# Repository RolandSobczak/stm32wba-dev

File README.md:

# wb55-dev

Dev board na **STM32WB55CGU6** (Bluetooth 5.x + 802.15.4) z pełnym torem
zasilania przeniesionym z `gps_tracker-6l`, pamięcią masową na płytce, anteną
w laminacie i wszystkimi wolnymi nóżkami na goldpinach 2,54 mm.

```
USB-C ──▶ BQ25896 ──┬──▶ SYS ──▶ TPS63020 ──▶ 3V3 ──┬──▶ STM32WB55CGU6 ──▶ MLPF ──▶ antena PCB
  │  (Rd 5.1k + ADC) │                              │        │
  └── D+/D- ─────────│──────────────────────────────│────────┘
                     └──▶ Li-Po 1S                  ├──▶ SD NAND 2 Gbit (SPI1)
                          │                         │
                          └──▶ BQ27441 (gauge)      └──▶ dwie listwy 1×12 (2,54 mm)
                                  │
                                  └── I2C1 ─────────────────┘
```

Obrys 32,5 × 59,6 mm, sześć warstw, narożniki R2,0, **dwa zestawy otworów**:
cztery M3 (⌀3,2) odsunięte 3,5 mm od krawędzi
po obrysie 25,8 × 42,2.

## Co jest wzięte z `gps_tracker-6l`

Tor zasilania w całości, razem z komentarzami uzasadniającymi — one są
w tych plikach wartością, a nie dekoracją:

| blok | część | skąd |
|---|---|---|
| gniazdo USB-C + ESD | GCT USB4085-GF-A, USBLC6-2SC6 | `power.ato` |
| ładowarka NVDC | TI BQ25896 (I2C 0x6B) | `power.ato` |
| gauge | TI BQ27441-G1A (I2C 0x55), bocznik 10 mΩ po stronie dodatniej | `power.ato` |
| 3V3 | TI TPS63020, buck-boost | `power.ato` |
| gniazdo ogniwa | Molex PicoBlade 53261-0371 — **ten sam pakiet wchodzi w obie płytki** | `power.ato` |
| stos | JLC06161H-7628, prepreg 0,2104 mm pod F.Cu | `tools/board_setup.py` |
| obrys, otwory, wylewki, klasy sieci | — | `tools/board_setup.py` |

Zmieniły się trzy rzeczy i każda ma powód w pliku:

1. **CC bez PD.** STM32WB55 nie ma UCPD (potwierdzone listą peryferiów
   w `STM32WB55CGUx.xml`). Zamiast negocjacji PD: dwa Rd 5,1 kΩ i pomiar
   napięcia na obu CC przetwornikiem — źródło USB-C ogłasza swój prąd prądem
   Rp niezależnie od PD. Szczegóły, progi i sekwencja dla firmware'u:
   [Zasilanie z USB](#zasilanie-z-usb--co-ustala-prąd-wejściowy).
   Efekt uboczny jest korzystny: Rd działa też przy martwym procesorze,
   więc płytka prosto z montażu dostaje VBUS.
2. **Dzielnik VBUS_SENSE wypadł** — bez maszyny stanów PD nie ma czego nim
   mierzyć w milisekundach, a napięcie VBUS czyta ADC ładowarki po I2C.
3. **Gauge `DRZR` → `DRZT`** — ten sam układ, inna nawijka. `DRZR` ma na LCSC
   stan 0.

## BOM

34 pozycje, wszystkie na stanie LCSC (sprawdzone 2 października 2026),
około **$30,50** za komplet części na jedną sztukę w cenach detalicznych.
Najdroższe: STM32WB55CGU6 $9,04 · SD NAND $8,66 · BQ25896 $3,52 ·
BQ27441 $2,52 · USB-C $1,41.

Pełna lista: `build/builds/dev/dev.bom.csv` (powstaje przy `ato build`).

Trzy pozycje odziedziczone z trackera miały na LCSC stan zero i zostały
podmienione — w komentarzach przy nich stoją nowe numery:

| było | jest | dlaczego |
|---|---|---|
| C25804 10 kΩ | **C98220** YAGEO RC0603FR-0710KL | stan 0 |
| C96446 10 µF 25 V | **C479655** 0603X106M250NT | stan 0 |
| C346479 bocznik 10 mΩ | **C105362** FMF06FTHR010-LH | stan 0; nowy ma ±1 %, 1 W i TCR ±70 ppm/°C, czyli lepiej niż poprzednik |

Poza BOM-em (kupowane osobno albo niekupowane wcale): dwie listwy goldpinów
1×12 2,54 mm, złącze SWD Samtec SHF-105-01-L-D-RA, cztery pady pomiarowe
i antena — ta ostatnia jest kształtem miedzi, nie elementem.

## Mapa wyprowadzeń

Układ ma **30 nóżek I/O i wszystkie są rozdane.** Siedem wolnych wychodzi
na prawą listwę, PA15 na lewą jako CS, PB5 na diodę.

```
 1 VBAT   +3V3           17 PA8   USART1_CK      33 VLXSMPS SMPS
 2 PC14   LSE_IN         18 PA9   USART1_TX      34 VDDSMPS +3V3
 3 PC15   LSE_OUT (0R)   19 PB2   CHG_STAT       35 VDD     +3V3
 4 PH3    BOOT0          20 VDD   +3V3           36 PA10    USART1_RX
 5 PB8    PMIC_SCL       21 RF1   -> MLPF        37 PA11    USB_D_N
 6 PB9    PMIC_SDA       22 VSSRF GND            38 PA12    USB_D_P
 7 NRST   reset          23 VDDRF +3V3           39 PA13    SWDIO
 8 VDDA   +3V3           24 OSC_OUT 32 MHz       40 VDDUSB  +3V3
 9 PA0    CC1 (ADC_IN5)  25 OSC_IN  32 MHz       41 PA14    SWCLK
10 PA1    CC2 (ADC_IN6)  26 AT0   bez sieci      42 PA15    EXT_CS
11 PA2    LPUART1_TX     27 AT1   bez sieci      43 PB3     SWO
12 PA3    LPUART1_RX     28 PB0   CHG_INT        44 PB4     GAUGE_INT
13 PA4    SD_CS          29 PB1   CHG_CE         45 PB5     LED
14 PA5    SD_CLK         30 PE4   CHG_PG         46 PB6     USART1 alt
15 PA6    SD_MISO        31 VFBSMPS SMPS         47 PB7     USART1 alt
16 PA7    SD_MOSI        32 VSSSMPS GND          48 VDD     +3V3
                                                 49 EP      GND  (jedyna masa!)
```

**Szycie liczy się z kształtem padu, nie z jego obrysem.** Pady termiczne
z EasyEDA to wielokąty: TPS63020 ma grzebień wycięć na nóżki, a BQ27441
kształt teowy ze środkową belką 2,0 × 1,95 mm i dwoma pionowymi pasami
szerokimi na 0,22 mm. Siatka rozłożona na prostokącie obrysu stawiałaby
przelotki w wycięciach — na gołym laminacie między nóżkami. Dlatego każda
pozycja jest sprawdzana dwa razy: czy **cała** przelotka mieści się
w miedzi padu (środek plus cztery punkty na obwodzie) i czy nie wchodzi
w cudzą miedź na którejkolwiek warstwie — przelotka jest przelotowa, więc
przebija też In2, In3 i B.Cu, gdzie leżą sygnały.

**Masa układu jest wyłącznie na padzie pod obudową** — UFQFPN-48 nie ma ani
jednej nóżki VSS. Pad dostaje **siatkę 5×5 = 25 przelotek** 0,50/0,30 mm
w rastrze 1,12 mm, stawianą przez `tools/board_setup.py`. Bez niej masa
procesora wisiałaby na wylewce F.Cu, a płaszczyzna In1 leży 0,2104 mm niżej.

**Przelotki leżą w padzie, więc muszą być zalane — i to przesądziło o liczbie
warstw.** Kanał przelotki ⌀0,3 przez laminat 1,6 mm ma 0,113 mm³; na padzie
5,5 × 5,5 mm leży przy szablonie 0,12 mm i pokryciu 60 % około 1,09 mm³
solderu. Czyli **już dziewięć otwartych przelotek ma pojemność porównywalną
z całym solderem**, a dwadzieścia pięć — dwa i pół raza większą. Niezalana
siatka oznacza zagłodzoną spoinę, a tu jest to jedyna masa układu.

Wycena JLCPCB (100 × 100 mm, 5 szt., FR-4 1,6 mm):

| konfiguracja | Via Covering | Via Plating | razem |
|---|---|---|---|
| 4 warstwy, Plugged albo Untented | €0,00 | — | **€7,13** |
| 4 warstwy, **Epoxy Filled & Capped** | €15,85 | €3,06 | **€26,03** |
| 6 warstw, Epoxy Filled & Capped (domyślne) | €0,00 | €0,00 | **€28,52** |

Dopłata na czterech warstwach to **€18,91**; „Horizontal Electroless Copper
Plating" (€3,06) jest przy zalewaniu wymuszone. **Stąd sześć warstw**: za
€2,49 różnicy zalewanie wchodzi w cenę, a przy okazji dochodzą dwie warstwy
sygnałowe (In2, In3).

Dwa haczyki, oba przy zamawianiu, nie w pliku płytki: produkcja trwa **8–9
dni** zamiast 3–4 (skrócenie do 3–4 kosztuje €118,01), a sześć warstw **nie
obsługuje HASL** — zostaje OSP albo ENIG. Przy rastrze 0,5 mm i padzie
termicznym ENIG i tak jest sensowniejszy, bo daje płaskie pady.

**Wszystkie wiertła mają 0,3 mm i ani dziesiątej mniej.** W formularzu
JLCPCB „Min via hole size/diameter" tylko pierwszy próg — `0.3mm/(0.4/0.45mm)`
— jest bezpłatny; każdy niższy podnosi cenę całego zamówienia. Dlatego
przelotka sygnałowa to **0,5/0,3** (a nie 0,6/0,3 jak wcześniej — próg
dopuszcza średnice od 0,4 mm, więc 0,1 mm wraca na trasowanie), a ta w padzie
**0,5/0,3** z sufitem narzuconym przez samo JLCPCB: *„Vias should be at most
0.5 mm in diameter to avoid incomplete filling. Vias violating this size will
be left unfilled."*

`board_setup.py` sprawdza to przy każdym uruchomieniu i wypisuje każdą
przelotkę z wiertłem poniżej progu — razem z pozycją i siecią.

Listwy (opis i uzasadnienie kolejności w `headers.ato`):

```
LEWA / J2 (SPI1 + rozszerzenia)     PRAWA / J1 (zasilanie, I2C, GPIO)
 1 SD_CLK    7 GND                   1 +3V3       7 PB6
 2 PA9       8 SD_MOSI               2 PA3        8 PB7
 3 PA10      9 GND                   3 PA8        9 PA2
 4 GND      10 EXP_P4                4 PMIC_SCL  10 +3V3
 5 EXT_CS   11 EXP_P5                5 GND       11 GND
 6 SD_MISO  12 EXP_P6                6 PMIC_SDA  12 BOOT0
```

Układ pozycji powstał przy trasowaniu, nie przy planowaniu — kolejność
widać dopiero wtedy, gdy linie zaczynają się krzyżować. Przeniesieniem
tego z płytki z powrotem do `.ato` zajmuje się `tools/sync_headers.py`.

**Na lewej listwie nie ma zasilania, tylko masa** (pozycje 4, 7, 9).
+3V3 przeniosło się w całości na prawą, gdzie stoi na dwóch pozycjach
(1 i 10) razem z dwiema masami (5 i 11) — przy listwie, z której coś się
zasila, jedna para na dwanaście pozycji oznacza długą drogę powrotną.
`VBUS` i `SYS` zniknęły z listew; obie sieci nadal są na płytce, tylko
nie wychodzą na goldpiny.

**Trzy zapasowe wyprowadzenia ekspandera (P4, P5, P6) wyszły na J2.**
P3 i P7 zostają na płytce. Osiem wyprowadzeń po drugiej stronie I2C jest
więcej warte na listwie niż w powietrzu.

### Jakie magistrale z tego wychodzą

Lista peryferiów w `STM32WB55CGUx.xml` kończy się na **I2C1, I2C3, USART1,
LPUART1, SPI1, QUADSPI**. Nie ma SPI2, nie ma I2C2, nie ma USART2 — na
większej obudowie STM32WB55 ma SPI2, ale jego nóżki (PB12–PB15, PC2/PC3,
PD0–PD4) nie wychodzą poza kostkę w UFQFPN-48.

| magistrala | nóżki | gdzie |
|---|---|---|
| **LPUART1** | PA2 / PA3 | J1-2, J1-3 |
| **USART1** | PA9 / PA10, albo PB6 / PB7 | J1-5/6 albo J1-9/10 |
| **I2C1** | PB8 / PB9 | J1-7, J1-8 |
| **SPI1** | PA5 / PA6 / PA7 + CS PA15 | J2-5/6/8 + J2-9 |

**QUADSPI jest tu martwy.** `QUADSPI_CLK` istnieje wyłącznie na PA3, a PA3 to
jedyny możliwy `LPUART1_RX` (drugi, PA12, to USB D+). `BK1_IO0` tylko na PB9,
`BK1_IO1` tylko na PB8 — czyli na magistrali PMIC-a. Włączenie QSPI
kosztowałoby drugi UART i sterowanie ładowarką naraz.

**Drugie SPI, gdyby było potrzebne**, ma dwie drogi i wykluczają się: dwa
układy na jednej magistrali SPI1 (SD NAND na PA4, zewnętrzny na PA15 — i to
przewiduje ta płytka), albo **USART1 w trybie synchronicznym** — `USART1_CK`
na PA8 robi z niego mastera SPI (PA8 jako SCK, PA9 jako MOSI, PA10 jako
MISO), kosztem drugiego UART-u i przy ~8 Mbit/s zamiast 32. Obie
konfiguracje chodzą na tych samych pozycjach listwy, więc przejście między
nimi to zmiana w firmware, nie przelutowanie.

**I2C na listwie TO JEST magistrala zasilania.** J1-7 i J1-8 to ta sama para,
na której wiszą BQ25896 (0x6B) i BQ27441 (0x55). Drugiej nie ma: I2C3 ma na
tym pakiecie po jednej nóżce na sygnał (`SCL` tylko PA7, `SDA` tylko PB4)
i obie są zajęte. Trzy konsekwencje opisane w nagłówku `headers.ato`: adresy
`0x6B` (kolizja z IMU ST) i `0x55` są zajęte, zwarcie na przewodzie zabiera
sterowanie ładowarką (watchdog I2C 40 s cofa ją do 500 mA), a pull-upy 4,7 kΩ
są dobrane pod płytkę — 20 cm przewodu spycha magistralę ze 400 na 100 kHz.

**Magistrala SPI1 na lewej listwie to ta sama, na której siedzi SD NAND**,
i inaczej się nie da: `SPI1_SCK` istnieje tylko na PA1 (CC2), PA5 (SD_CLK)
i PB3 (SWO), a `SPI1_MISO` tylko na PA6 (SD_MISO), PA11 (USB) i PB4
(GAUGE_INT) — ani jednej wolnej nóżki.

Pozycje 5–9 lewej listwy były puste — niosły SWD, zanim na płytkę weszło
osobne złącze ARM Cortex Debug 2×5. Wcześniejsza wersja tego opisu zakazywała
ich ponownego użycia; **ten argument wiąże dopiero od pierwszej
wyprodukowanej sztuki**, a takiej nie ma.

Wejście w DFU: zworka z pinu 11 (BOOT0) na pin 3 (+3V3) lewej listwy i reset.

## Przyciski i diody

Opis i uzasadnienia w `ui.ato`. Dwie warstwy, bo dwie klasy problemów.

### Przyciski systemowe — zero nóżek procesora

| przycisk | podłączenie | co już było na płytce |
|---|---|---|
| **RESET** (`SW1`) | NRST → masa | 100 nF + 100 k podciągnięcie z `mcu.ato` |
| **BOOT0** (`SW2`) | BOOT0 → +3V3 | 10 k ściągnięcie z `mcu.ato` |

NRST i BOOT0 to nie GPIO, więc te przyciski nie kosztują ani jednego
wyprowadzenia. Nie wprowadzają też **ani jednej nowej sieci** — obie
końcówki wiszą na `NRST`, `BOOT0`, `GND` i `+3V3`. Gest jest standardowy:
trzymasz BOOT0, stukasz RESET, jesteś w bootloaderze. Wcześniej reset
wymagał zwarcia pinów listwy albo odcięcia zasilania, a DFU — drutu z J2-11
na J2-3.

Przycisk: **C&K KMR221GLFS** (C72443), gull-wing, 4,6 × 2,8 × 1,9 mm,
50 mA / 100 000 cykli. Ekran (nóżka 5) idzie na masę — nielutowany zbiera
ładunek z palca i oddaje go w sygnał, co przy RESET oznacza płytkę
resetującą się od dotknięcia obok.

Rezystora 100 Ω szeregowo przy RESET **nie ma świadomie**: przycisk zwiera
naładowane 100 nF przez styki, co je powoli eroduje, ale AN2586 i wszystkie
płytki Nucleo oraz Discovery łączą go wprost.

### Ekspander I/O — TCA6408A

VQFN-16 **3,0 × 3,0 mm** (LCSC C181499), na magistrali zasilania pod
**adresem 0x20** (ADDR na masie), czyli daleko od ładowarki `0x6B`
i gauge'a `0x55`.

```
P0  dioda czerwona      P4  wolne
P1  dioda zielona       P5  wolne
P2  przycisk użytk.     P6  wolne
P3  wolne               P7  wolne
```

Dwie diody i jeden przycisk, nie trzy i dwa — wersja z trzema diodami
i dwoma przyciskami zajmowała 166,5 mm² i nie mieściła się w wolnych
kieszeniach płytki.

Wybrany po czterech liczbach z noty: **wyjścia przeciwsobne** (PCF8574
podciąga tylko ~100 µA i wymusza logikę „zapalone = nisko"), **1,65–5,5 V**,
**1,5 µA w spoczynku** — ta ostatnia przesądziła o rezygnacji z diody
adresowalnej, bo sterownik WS2812 pobiera rzędu 1 mA nawet zgaszony —
i **obrys 3,4 × 3,4 mm**.

Pierwotnie stał tu TCA9534PWR w TSSOP-16: funkcjonalnie to samo, ale
**32 mm² zamiast 11**, czyli trzykrotnie więcej. Na płytce, której
największy wolny blok ma 13 × 8,5 mm, to była różnica między „wchodzi"
a „nie wchodzi".

Obudowa QFN kosztuje trzy rzeczy, których TSSOP nie wymagał — dwie szyny
zasilania (`VCCI` i `VCCP`, obie na +3V3), nóżkę `RESET` (zwarta wprost do
szyny) i pad pod obudową (na masę, zszywany przelotkami jak pozostałe).
Żadna z nich nie kosztuje dodatkowego elementu. Raster zostaje 0,5 mm,
czyli taki sam jak w procesorze.

Nóżka adresowa jest jedna zamiast trzech, więc adresy są dwa — `0x20`
i `0x21`. Przy jednym ekspanderze to niczego nie ogranicza.

`nINT` jest otwartym drenem i ma własne 10 k; idzie na **PB5**. Przerwanie
nie potrzebuje żadnej funkcji alternatywnej, a PB5 żadnej użytecznej nie ma
— stąd para. EXTI budzi ze Stop; ze Standby nie, bo do tego trzeba nóżek
WKUP, a te są dwie i obie zajęte.

Przycisk ma **podciągnięcie zewnętrzne 10 k**, bo TCA6408A nie ma
wewnętrznych.

**Pięć wolnych wyprowadzeń nie ma rezystorów i to jest kontrakt
z firmware'em.** Nota daje dwie drogi — rezystor na każde wejście, które
może pływać, albo ustawienie tych wyprowadzeń jako wyjść (*„Outputs do not
need pull-up resistors"*). Pięć sztuk 0603 to 21,5 mm² wydane na nic;
jedna linijka w inicjalizacji kosztuje zero. Cena: do pierwszego zapisu
rejestru konfiguracji nóżki pływają, a pływające wejście CMOS ciągnie do
~100 µA — płytka w szufladzie z ogniwem i bez działającego programu będzie
to brać cały czas.

**Wszystkie nóżki donikąd mają nazwy sieci** (`EXP_P3_NC`…`EXP_P7_NC`,
`SD_DAT1_NC`, `SD_DAT2_NC`, `AT0_NC`, `AT1_NC`). Bez nich atopile nazywa
je numerem nóżki, a numer potrafi wejść w kolizję z numeracją, na którą
wskazują wylewki — raz skończyło się to trzema wylewkami masy pokazującymi
na sieć `7`, czyli na wolne wyprowadzenie ekspandera.

Diody: czerwone `NCD1206R1` (C84270) i zielona `NCD1206C1` (C84273), 1206,
przez 1 kΩ (C21190) — **1,4 mA**. Uwaga przy podłączaniu: **te dwie diody
mają odwrotnie numerowane nóżki** (czerwona ma anodę na 1, zielona na 2),
choć fizycznie obie mają anodę na padzie po prawej. Łączyć po nazwach
sygnałów, nigdy po numerach.

## SWD

**Samtec SHF-105-01-L-D-RA** (`CN1`) — standardowy ARM Cortex Debug Connector
2×5 w rastrze 1,27 mm, kątowy, przewlekany, w kołnierzu z kluczem. Kabel
J-Link EDU Mini wchodzi w niego wprost; ten sam kabel obsługuje ST-LINK V2/V3
i większość sond innych producentów.

```
1 VTref (+3V3)   2 SWDIO
3 GND            4 SWCLK
5 GND            6 SWO
7 KEY            8 NC (TDI)
9 NC (TRST)     10 NRST
```

Dwie masy leżą **między** szybkimi liniami (pin 3 między SWDIO i SWCLK, pin 5
między SWCLK a SWO), więc każda ma drogę powrotną w sąsiedniej żyle taśmy —
przy SWO, którym idzie konsola ITM, od tego zależy, przy jakiej częstotliwości
strumień przestaje się sypać.

**VTref to wejście sondy, nie zasilanie płytki.** J-Link EDU Mini nie zasila
celu i pobiera z tego pinu mniej niż 170 µA, więc płytka musi być zasilona
z USB-C albo z ogniwa — inaczej sonda jej nie zobaczy, a wygląda to dokładnie
jak martwy procesor.

## Jak to zbudować

Wszystko w kontenerze — `tools/boards.py` wywala się na hostowym `pcbnew`,
bo KiCad 10 podniósłby format płytki jednokierunkowo:

```bash
distrobox enter -n atopile -- ato build -b dev           # netlista + projekt KiCada
python3 tools/check_pinout.py                            # mapa nóżek wobec danych ST
distrobox enter -n atopile -- python3 tools/board_setup.py
```

`board_setup.py` jest idempotentny i trzeba go puszczać **po każdym**
`ato build` — `ato` nadpisuje plik płytki i gubi przy tym `net_tie_pad_groups`
anteny. Skrypt ustawia:

* stos 6-warstwowy (In1 = `GND`, **In4** = `PWR`, In2/In3 sygnałowe), bez niego
  tor RF liczyłby się na ~120 Ω zamiast 50,
* obrys 32,5 × **60,6** mm z narożnikami R2,0, lewym górnym rogiem w (8,41 / 2,30)
  i **czterema otworami ⌀3,2 (M3)** odsuniętymi 3,5 mm od obu krawędzi.
  Płytka urosła o 1 mm **w górę**: dolna krawędź i wszystko, co rozmieszczone,
  zostało na miejscu, a miejsce przybyło przy antenie — na odsunięcie filtra
  MLPF i na przelotkę zwierającą. Przeciwwaga anteny rośnie z 59,6 na 60,6 mm,
  czyli o 1,7 %, i tak będąc dwukrotnie większa od ćwierci fali (30,6 mm).
  Zestaw ⌀2,0 odziedziczony po obrysie 25,8 × 42,2 **został usunięty** —
  zabierał miejsce potrzebne elementom, a żaden stary uchwyt nie jest tego
  wart. Najcieńsza obwódka laminatu: 1,90 mm,
* wylewki masy na F.Cu i B.Cu, płaszczyzny na In1 i In4,
* klasy sieci — m.in. **RF 0,39 mm przy odstępie 0,15** (`RF1`, `ANT`) i **USB 0,28 mm**
  (`USB_D_P`/`USB_D_N` przy procesorze, `USB_CONN_P`/`USB_CONN_N` przy
  gnieździe — przyrostki `_P`/`_N` są warunkiem, żeby KiCad w ogóle
  rozpoznał parę różnicową),
* **przelotkę zwierającą radiator anteny do płaszczyzny masy** — stawianą
  w padzie lądowania, wybieranym geometrycznie: musi pomieścić całą
  przelotkę z odstępem i leżeć **poniżej strefy zakazu**, czyli już
  w obszarze masy. Pionowy zwieracz też mieści przelotkę (0,90 mm
  szerokości), ale siedzi w strefie zakazu — przelotka w nim byłaby masą
  dokładnie tam, gdzie masy być nie może,
* **pad lądowania 1,10 × 1,10 mm pod zwieraczem anteny** — jedyny prostokąt
  spoza Table 1 noty AN043. Stopa zwieracza z noty ma 0,90 × 0,50 mm, a
  przelotka 0,5 mm z odstępem potrzebuje 0,80 w obu osiach, więc przelotka
  zwierająca — zakładana przez komentarz przy `ANTENA_KEEPOUT_MM` od początku
  — nigdy nie miała się gdzie zmieścić. Zwarcie radiatora do masy jest całą
  zasadą działania odwróconej F; bez niego to kawałek miedzi o nieokreślonej
  impedancji. Wymiarów samej anteny nie ruszono,
* **sitodruk sprowadzony do minimum JLCPCB** — producent podaje jako absolutne
  minimum **0,8 mm wysokości znaku i 0,15 mm szerokości kreski** (zaleca 1,0 / 0,2).
  Oznaczenia elementów idą na 0,80 × 0,15; napisy własne, czyli mapa pinów listew,
  zachowują swoją wysokość 1,0 mm i dostają poprawioną samą kreskę — to one są
  czytane przy wpinaniu przewodu. Poniżej 0,15 mm JLCPCB i tak pogrubia kreskę
  sam, tyle że bez zachowania proporcji znaku: przy literze wysokiej na 0,5 mm
  (tyle miało 25 oznaczeń) proporcja robi się 1:3 zamiast zalecanego 1:6
  i wychodzi plama,
* **strefę zakazu 15,2 × 5,2 mm pod anteną na wszystkich sześciu warstwach**,
* **szycie przelotkami pod padami termicznymi** obudów bez nóżek (QFN/SON/DFN)
  leżącymi na masie: `U1` 5×5 = 25 przelotek w padzie 5,50 × 5,50 mm,
  `U4` 2×2 = 4 w padzie 2,70 × 2,70. Przelotki 0,50/0,30 mm, margines do
  krawędzi padu 0,25 mm. Siatka idzie za rozmieszczeniem — przesunięcie
  albo obrócenie układu przenosi ją razem z nim,
* `net_tie_pad_groups "1, 2"` na antenie, żeby DRC nie zgłaszał zwarcia
  ANT–GND (w antenie typu F to zwarcie jest zamierzone).

## Antena

TI AN043 (SWRA117D), odwrócone F, 15,2 × 5,7 mm, VSWR < 2 w całym paśmie ISM.
Geometria przepisana co do setnej z Table 1 noty i sprawdzona rachunkiem —
`L3 = W1+D5+W2+D6+W2 = 5,00` oraz gabaryt `15,20 × 5,70` muszą się domknąć
i domykają się (`parts/Antenna_IFA_2G4/Antenna_IFA_2G4.ato`).

Między RF1 a anteną stoi **jedna** część: `MLPF-WB55-01E3`, scalona sieć
dopasowania ST z filtrem harmonicznych. AN5165 §7: zastępuje dyskretny
matching (0,8 pF + 2,7 nH + 0,3 pF) razem z osobnym filtrem, przy
równoważnych parametrach. Nie ma tu czego stroić.

**Do zmierzenia na pierwszej sztuce.** Nota mierzyła tę antenę na laminacie
dwuwarstwowym 1,6 mm; tutaj laminat ma tyle samo, ale masa biegnie 0,21 mm
pod warstwą górną — pod samą anteną wycięta, więc różnica dotyczy głównie
pojemności brzegowej. Kierunek ewentualnej poprawki podaje nota: grubszy
laminat → antena krótsza.

## Co zostało do zrobienia

Projekt dowozi źródło, netlistę, stos, obrys z otworami, klasy sieci
i footprint anteny. **Rozmieszczenie i trasowanie to robota w KiCadzie** —
wszystkie elementy stoją na razie w domyślnych pozycjach z `ato build`.

Czego pilnować przy rozmieszczaniu (uzasadnienia w nagłówku `dev.ato`):

* procesor, oba kwarce, cewki SMPS i cała droga RF **na F.Cu**, nad litą
  masą In1 — AN5165 §4.3,
* antena na krótszej krawędzi, wyśrodkowana między górnymi otworami M3,
  zwrócona na zewnątrz; między nimi zostaje ~24 mm luzu na 15,2 mm anteny,
* MLPF tuż przy procesorze, odcinek 50 Ω do anteny najkrótszy, jaki wyjdzie,
* USB-C i gniazdo ogniwa na przeciwnej krawędzi — najdalej od anteny,
* pętla SMPS (`VDDSMPS → VLXSMPS → 10 nH → 10 µH → VFBSMPS`) krótka i w całości
  na F.Cu,
* obrys przeszedł trzy wersje i każda jest w komentarzu w
  `tools/board_setup.py`: **38 × 50** (szacunek z sumy powierzchni, przed
  rozmieszczeniem), **25,8 × 42,2** (po pierwszym rozmieszczeniu), **51,6 × 84,4**
  (×2 — przesada), **38,7 × 63,3** (×1,5) i **32,5 × 59,6** (docięte ręcznie
  pod rozmieszczenie i tu wyrównane).
* **Otwory M3 nie są współśrodkowe z narożnikami.** Historycznie wynikało to
  z kolizji z zestawem ⌀2,0 — oba wypadały 1,49 mm od siebie przy wymaganych
  2,60 i zlewały się w jedną dziurę. Zestaw ⌀2,0 od tego czasu zniknął, ale
  odsunięcie zostało: przy rozmieszczaniu okazało się, że przy 4,5 mm łebki
  śrub wchodzą w pole potrzebne elementom, więc odstęp zszedł na **3,5 mm**.
* Narożnik ma **R2,0, nie R2,5** — to też pozostałość po zestawie ⌀2,0,
  któremu łuk wyznaczał obwódkę (0,18 mm przy R2,5 wobec 0,36 przy R2,0).
  Przy samych M3 w 3,5 mm od krawędzi obwódka wynosi 1,90 mm i promień
  narożnika przestał ją ograniczać.
  Wymiary i położenie rogu siedzą w stałych `BOARD_X_MM` / `BOARD_Y_MM` /
  `DEFAULT_W_MM` / `DEFAULT_H_MM`, żeby skrypt je **odtwarzał**, a nie
  nadpisywał — inaczej pierwsze uruchomienie po ręcznej poprawce
  skasowałoby ją bez słowa.
* płytka rośnie **w prawo i w dół**, róg zostaje w (8,78 / 3,30) — dzięki
  temu powiększenie nie rusza niczego, co już rozmieszczone, a zestaw
  otworów ⌀2,0 zostaje tam, gdzie był.

Potem DRC na regułach JLCPCB (0,127/0,127, wiertło 0,2).

## Pliki wytwórcze

```bash
distrobox enter -n atopile -- python3 tools/fabrication.py --board dev
```

Źródłem jest **plik płytki z repozytorium**, nie przebudowa z atopile — w gicie
leży to, co faktycznie idzie do produkcji, razem z ręczną miedzią i wylewkami.
Uruchamiać **po** `tools/board_setup.py`, bo to on nadaje wylewkom sieć, wylewa
je i stawia przelotki.

Powstaje w `build/fab-dev/`:

| plik | co to | wgrywać do JLC? |
|---|---|---|
| `gerbers.zip` | 16 plików: sześć warstw miedzi, pasty, sitodruki, maski, obrys, PTH + NPTH | **tak** |
| `bom_montaz_jlc.csv` | 9 pozycji — to, czego nie da się polutować grotem | **tak**, przy montażu |
| `cpl_montaz_jlc.csv` | pozycje tych samych 9 części | **tak**, przy montażu |
| `bom_zakupy.csv` | 39 pozycji, 77 sztuk — **wszystko z numerem LCSC**, z ilościami i kolumną `Montaz` | nie, to lista zakupów |
| `cpl_wszystko.csv` | pozycje wszystkich 77 części | nie, zapasowo |
| `montaz_recznie.csv` | 7 części bez numeru LCSC — listwy, złącze SWD, pady pomiarowe | nie |
| `plytka.pdf` / `plytka.step` | podgląd warstw i model 3D | nie |

### Co idzie do montażu, a co pod grot

JLCPCB montuje **tylko obudowy leadless** (QFN, SON, DFN, LGA) plus `FL1`
i oba kwarce — razem dziewięć sztuk:

```
U1  VQFN-48   STM32WB55      U7  QFN-16      TCA6408A
U3  VSON-14   TPS63020       FL1 FILTER-SMD  MLPF-WB55-01E3
U4  QFN-24    BQ25896        X1  CRYSTAL 2,0 x 1,6 mm
U5  SON-12    BQ27441        X2  CRYSTAL 3,2 x 1,5 mm
U6  LGA-8     SD NAND
```

Te obudowy nie mają nóżek — pady są pod spodem i bez szablonu z pastą nie
ma do nich dostępu, a pod procesorem siedzi jeszcze pad termiczny z 22
przelotkami. `FL1` ma sześć padów w rastrze 0,50 mm na obudowie
1,6 × 1,0 mm i leży w torze RF, gdzie zimny lut objawia się brakiem
zasięgu, a nie błędem. Źle przylutowany kwarc nie startuje wcale.

Reszta — 30 pozycji, 68 sztuk — idzie ręcznie. Przy 0603 i większych to
kwadrans roboty, a każda pozycja w montażu to osobna opłata za podajnik.

**Przemianowanie warstw wewnętrznych nie jest kosmetyką.** `kicad-cli` nazywa
gerber nazwą *użytkownika* warstwy, a nasze nazywają się `GND` i `PWR` — fab
takich nie zna. Skrypt zmienia je na `In1_Cu`…`In4_Cu` i przy okazji poprawia
numerację w pliku zadania: KiCad 9 wpisuje tam swój wewnętrzny identyfikator
warstwy, przez co `In1_Cu` wychodziło jako `L5` zamiast `L2`. Wierzch i spód
numeruje poprawnie, więc błędu nie widać, dopóki nie policzy się warstw
wewnętrznych — a płytka przyszłaby z płaszczyznami nie tam, gdzie trzeba.

## Zasilanie z USB — co ustala prąd wejściowy

To jest miejsce, w którym najłatwiej szukać peryferialu, którego nie ma, więc
warto je przeczytać przed pisaniem firmware'u. Pełne uzasadnienie w nagłówku
`power.ato`.

**Nic na tej płytce nie „włącza" 3 A — źródło oferuje je samo.** Źródło USB-C
wystawia na CC **Rp**, i to jest deklaracja, nie negocjacja. Nasze Rd 5,1 kΩ
zamienia ją na napięcie stałe:

| co źródło daje przy 5 V | Rp (rezystor / źródło prądowe) | na Rd 5,1 kΩ | okno odczytu |
|---|---|---|---|
| Default USB (500/900 mA) | 56 kΩ do 5 V / 80 µA | 0,42 / 0,41 V | 0,25–0,61 V |
| 1,5 A | 22 kΩ do 5 V / 180 µA | 0,94 / 0,92 V | 0,70–1,16 V |
| 3,0 A | 10 kΩ do 5 V / 330 µA | 1,69 / 1,68 V | 1,31–2,04 V |

Przerwy między oknami (0,61–0,70 i 1,16–1,31 V) są martwe — pomiar, który
w nie wpadnie, ma zostawić poprzednią, **niższą** wartość.

VBUS jest żywe z pełną zadeklarowaną zdolnością od chwili, w której źródło
wykryje Rd. Nie trzeba o nie prosić; cała umowa polega na tym, że to
**odbiornik** pilnuje, żeby nie wziąć więcej. Interfejsem procesora są więc
**dwa kanały przetwornika** (PA0 = ADC1_IN5, PA1 = ADC1_IN6) i nic poza tym.
Mierzymy oba, bo przez kabel podłączony jest tylko jeden — ten z napięciem
mówi przy okazji, którą stroną wszedł wtyk.

Sam prąd wejściowy jest **minimum z trzech** rzeczy:

1. **rezystor na ILIM (121 Ω)** — sufit sprzętowy 2,64/2,93/3,22 A, nie do
   przeskoczenia zapisem po I2C,
2. **rejestr IINLIM** — po starcie 500 mA, bo PSEL wisi wysoko (USB SDP),
3. **ICO (Input Current Optimizer)** — sam podnosi prąd aż do progu, przy
   którym źródło zaczyna siadać, czyli **mierzy** zamiast wierzyć deklaracji.

ICO jest domyślnie włączony, ale **rusza sam tylko po wykryciu DCP** — przy
PSEL wysoko jesteśmy SDP, więc firmware musi go odpalić bitem `FORCE_ICO`
(REG09[7]). Bez tego najlepszy mechanizm w tej ładowarce po prostu nie
zadziała.

Pod spodem jest VINDPM: gdy źródło siada, ładowarka sama cofa prąd. Zbyt
optymistyczny IINLIM kończy się więc „ładuje wolniej", a nie zapadnięciem
szyny.

### Dlaczego nie ma tu układu PD

Bo nic by nie dał. Ogniwo przyjmie najwyżej 1,9 A (1C) ≈ 8 W, a przy wybranym
ICHG = 1,3 A z wejścia schodzi ~6,4 W, czyli **1,28 A przy 5 V**. Źródło
ogłaszające 3 A daje 15 W — ponad dwukrotny zapas. PD dołożyłoby wyższe
*napięcie*, a nie większą moc, a BQ25896 jest przetwornicą obniżającą.

Do tego dwa twarde sufity: **V(ACOV) ładowarki to 14 V** (próg z tabeli
parametrów, nie z rejestru), więc z PD użyteczne byłyby tylko 9 V i 12 V;
a **USBLC6-2SC6 ma napięcie przebicia VBUS–GND min. 6 V**, więc PD oznacza
też wymianę układu ESD, a nie dołożenie jednej kości.

Gdyby kiedyś miało to być stanowisko do zabawy z USB-PD, pierwszy wybór to
STUSB4500 (C2678061, QFN-24 4×4, ~$2,7) — negocjuje autonomicznie z NVM,
I2C 0x28 wchodzi na istniejącą magistralę obok ładowarki i gauge'a, bez
zabierania nóżki.

## Firmware — czego sprzęt oczekuje

* **SMPS startuje w trybie BYPASS** (DS11929 §3.7.1) — rdzeń żywi się z LDO
  i płytka wstaje nawet bez cewek. Tryb SMPS włącza firmware; to oszczędność
  prądu przy nadawaniu, nie warunek startu.
* **HSE 32 MHz bez kondensatorów obciążenia** — pojemność daje wewnętrzna
  banka `XOTUNE` (6 bitów, ±40 ppm). Tam też stroi się częstotliwość po
  pomiarze.
* **SD NAND w trybie SPI**: host musi ściągnąć `DAT3` (CS) do zera przy
  pierwszych taktach inicjalizacji, inaczej układ wybierze tryb SD.
  SPI1 na APB2 → maksymalnie 32 MHz SCK, realnie 2–3 MB/s.
* **Ładowarka** — sekwencja po wpięciu kabla:

  ```
  1. ADC na CC1/CC2    →  które okno z tabeli wyżej
  2. IINLIM := 500 mA / 1,5 A / 3,0 A      ← deklaracja źródła, sufit
  3. FORCE_ICO = 1                         ← ładowarka szuka maksimum POD tym sufitem
  4. odczyt IDPM_LIM i ICO_OPTIMIZED       ← ile naprawdę wyszło
  5. ICHG := 1300 mA (0,68 C)
  6. watchdog I2C co < 40 s
  ```

  Kroki 1–2 to zaufanie deklaracji, krok 3 to pomiar — warto zrobić oba.
  Rp może się zmienić w trakcie pracy (hub rozdzielający moc), więc odczyt
  CC powtarza się, a nie robi raz przy starcie.

  Watchdog: po 40 s bez odświeżenia rejestry wracają do domyślnych, czyli do
  500 mA na wejściu. Zawieszony firmware zostawia więc ogniwo ładowane za
  słabo, nie za mocno.

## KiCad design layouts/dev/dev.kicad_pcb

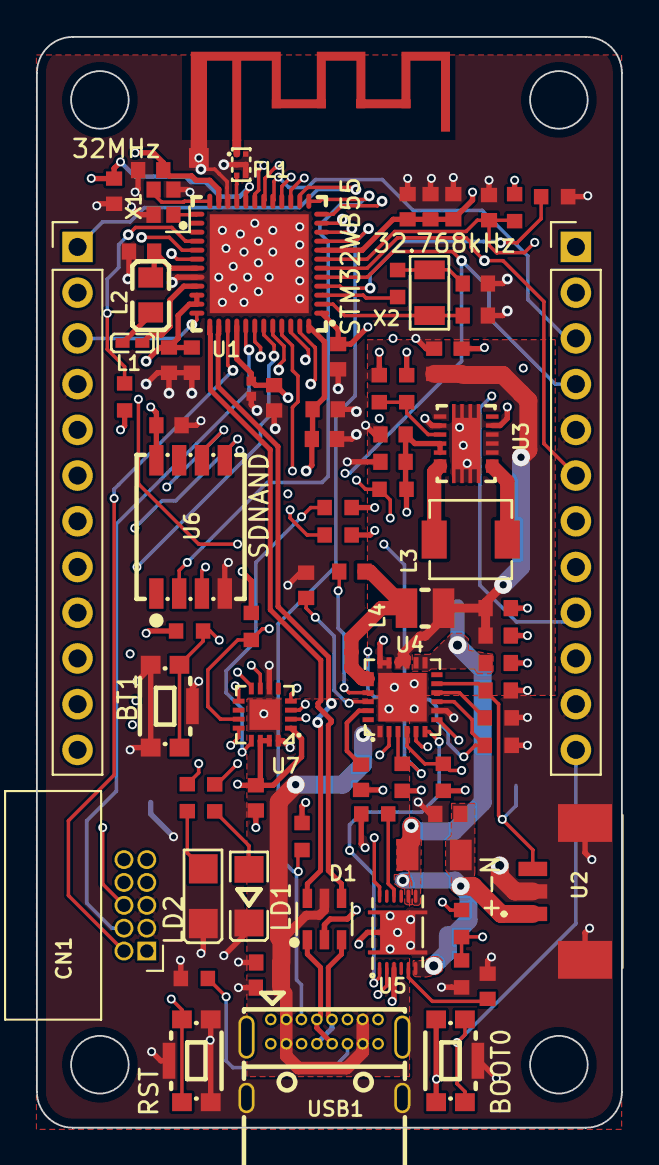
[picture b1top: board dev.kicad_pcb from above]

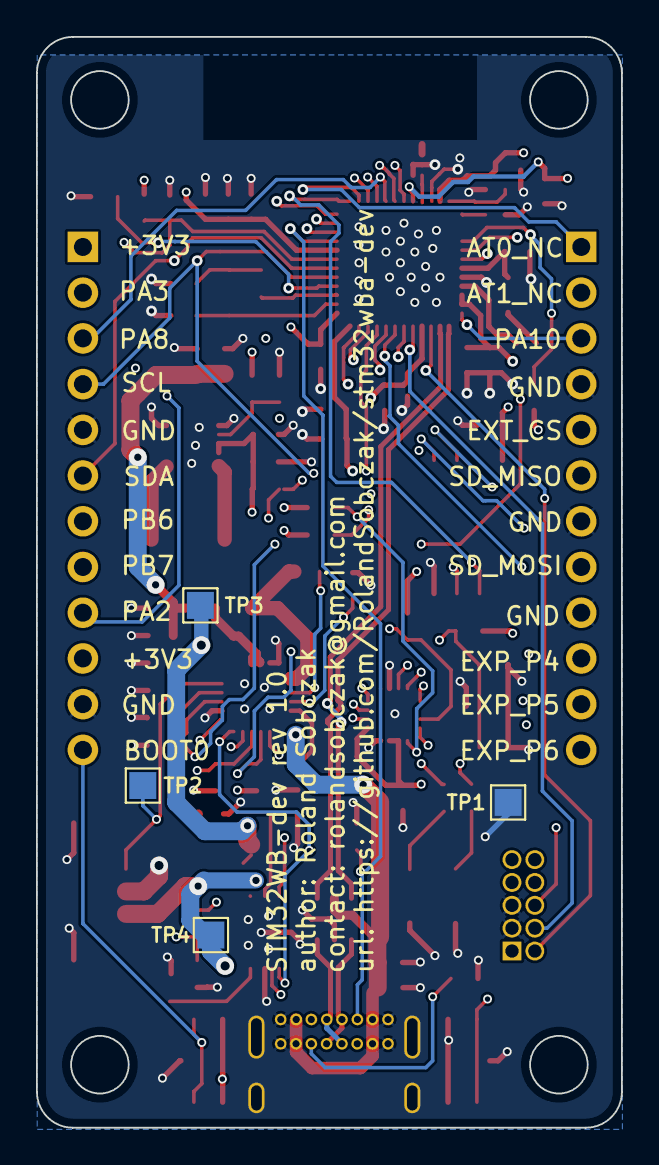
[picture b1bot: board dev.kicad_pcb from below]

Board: 6 copper layers, 32.5 x 60.6 mm, 85 parts (4 on the bottom side), 66 nets.

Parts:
AE1: Antenna_IFA_2G4
C1, C8, C9, C23: 4.7µF ±10%; C0603
C2, C3, C4, C7, C10, C12, C13, C15, C19, C26, C32, C33: 100nF ±10%; C0603
C5, C6: 12pF ±5%; C0603
C11, C27, C28, C29: 1µF ±10%; C0603
C14: 100pF ±5%; C0402
C16, C20, C22, C30, C31: 10µF ±20%; C0603
C17, C18, C24, C25: 22µF ±20%; C0603
C21: 47nF ±10%; C0603
CN1: CONN-THT_10P-P1.27_SHF-105-01-L-D-RA
D1: SOT-23-6_L2.9-W1.6-P0.95-LS2.8-BL
FL1: FILTER-SMD_6P-L1.6-W1.0-P0.50-BL
J1, J2: PinHeader_1x12
L1: L 10nH ±5%; L0402-RD
L2: L 10µH ±20%; L0805
L3: L 1.5µH ±20%; IND-SMD_L4.4-W4.2
L4: L 1µH ±20%; IND-SMD_L2.5-W2.0
LED1: LED1206-RD
LED3: LED1206-R-RD_RED
R1, R10, R14, R15, R16, R17, R20, R22: 10kΩ ±1%; R0603
R2: 0Ω; R0603
R3, R6: 100kΩ ±1%; R0603
R4: 180kΩ ±0.1%; R0603
R5: 1MΩ ±1%; R0603
R7: 121Ω ±0.1%; R0603
R8: 30kΩ ±0.5%; R0603
R9: 5.23kΩ ±1%; R0603
R11: 10mΩ ±1%; R1206
R12, R13: 4.7kΩ ±1%; R0603
R18, R19: 5.1kΩ ±1%; R0603
R23, R25: 1kΩ ±1%; R0603
SW1, SW2, SW3: KEY-SMD_KMR2XXGXXX
TP1, TP2, TP3, TP4: TestPoint_Pad_D1R5
U1: VQFN-48_L7.0-W7.0-P0.50-BL-EP5.5
U2: 532610371_Molex_PicoBlade_3Pin_1_25
U3: VSON-14_L4.0-W3.0-P0.50-BL-EP_TI_DSJ
U4: QFN-24_L4.0-W4.0-P0.50-TL-EP2.7
U5: SON-12_L4.0-W2.5-P0.40-TL-EP
U6: LGA-8_MKDV_handsolder
U7: QFN-16_L3.0-W3.0-P0.50-BL-EP1.7
USB1: USC-C-SMD_USB4085-GF-A
X1: CRYSTAL-SMD_4P-L2.0-W1.6-BL
X2: CRYSTAL-SMD_L3.2-W1.5-1

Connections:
+3V3: C1.1, C2.1, C3.1, C4.1, C8.1, C10.1, C11.1, C12.1, C13.1, C14.1, C15.1, C17.1, C18.1, C31.1, C32.1, C33.1, CN1.1, J1.1, J1.10, R3.1, R5.1, R12.1, R13.1, R14.1, R15.1, R16.1, R17.1, R20.1, R22.1, SW1.3, SW1.4, U1.1, U1.8, U1.20, U1.23, U1.34, U1.35, U1.40, U1.48, U3.4, U3.5, U6.8, U7.1, U7.14, U7.15
ANT: AE1.1, FL1.1
BIN: R10.1, U5.10
BOOT0: J1.12, R1.1, SW1.1, SW1.2, U1.4
BTN_USR: R20.2, SW3.1, SW3.2, U7.4
BTST: C21.1, U4.21
CC1: R18.1, U1.9, USB1.A5
CC2: R19.1, U1.10, USB1.B5
CHG_CE: R6.1, U1.29, U4.9
CHG_INT: R16.2, U1.28, U4.7
CHG_PG: R14.2, U1.30, U4.3
CHG_STAT: R15.2, U1.19, U4.4
EXP_INT: R22.2, U1.45, U7.11
EXP_LED0: R25.1, U7.2
EXP_LED1: R23.1, U7.3
EXP_P4: J2.10, U7.7
EXP_P5: J2.11, U7.8
EXP_P6: J2.12, U7.9
EXT_CS: J2.5, U1.42
FB: R4.1, R5.2, U3.3
GAUGE_INT: R17.2, U1.44, U5.12
GAUGE_VDD_1V8: C29.1, U5.5
GND: AE1.2, C1.2, C2.2, C3.2, C4.2, C5.2, C6.2, C7.2, C8.2, C9.2, C10.2, C11.2, C12.2, C13.2, C14.2, C15.2, C16.2, C17.2, C18.2, C19.2, C20.2, C22.2, C23.2, C24.2, C25.2, C26.2, C27.2, C28.2, C29.2, C30.2, C31.2, C32.2, C33.2, CN1.3, CN1.5, D1.2, FL1.2, FL1.4, FL1.5, FL1.6, J1.5, J1.11, J2.4, J2.7, J2.9, LED1.1, LED3.2, R1.2, R4.2, R6.2, R7.2, R8.2, R10.2, R18.2, R19.2, SW1.5, SW2.3, SW2.4, SW2.5, SW3.3, SW3.4, SW3.5, TP1.1, U1.22, U1.32, U1.49, U2.2, U2.4, U2.5, U3.2, U3.13, U3.15, U4.8, U4.17, U4.18, U4.25, U5.3, U5.13, U6.4, U7.6, U7.16, U7.17, USB1.A1, USB1.A12, USB1.B1, USB1.B12, USB1.S1, X1.2, X1.4
LED0_A: LED3.1, R25.2
LED1_A: LED1.2, R23.2
LIIM: R7.1, U4.10
LSE_IN: C5.1, U1.2, X2.1
LSE_OUT: R2.1, U1.3
LSE_XTAL: C6.1, R2.2, X2.2
NRST: C7.1, CN1.10, R3.2, SW2.1, SW2.2, U1.7
NTC: C26.1, R8.1, R9.2, TP2.1, U2.3, U4.11
OSC_IN: U1.25, X1.1
OSC_OUT: U1.24, X1.3
PA2: J1.9, U1.11
PA3: J1.2, U1.12
PA8: J1.3, U1.17
PA9: J2.2, U1.18
PA10: J2.3, U1.36
PB6: J1.7, U1.46
PB7: J1.8, U1.47
PMIC_SCL: J1.4, R12.2, U1.5, U4.5, U5.2, U7.12
PMIC_SDA: J1.6, R13.2, U1.6, U4.6, U5.1, U7.13
PMID: C22.1, U4.23
REGN: C23.1, R9.1, U4.2, U4.22
RF1: FL1.3, U1.21
SD_CLK: J2.1, U1.14, U6.3
SD_CS: U1.13, U6.2
SD_MISO: J2.6, U1.15, U6.6
SD_MOSI: J2.8, U1.16, U6.5
SMPS_MID: L1.2, L2.1
SWCLK: CN1.4, U1.41
SWDIO: CN1.2, U1.39
SWO: CN1.6, U1.43
SW_BAT: L3.1, U3.8, U3.9
SW_CHG: C21.2, L4.1, U4.19, U4.20
SW_OUT: L3.2, U3.6, U3.7
SYS: C16.1, C19.1, C24.1, C25.1, L4.2, U3.1, U3.10, U3.11, U3.12, U4.15, U4.16
USB_CONN_N: D1.3, USB1.A7, USB1.B7
USB_CONN_P: D1.1, USB1.A6, USB1.B6
USB_D_N: D1.4, U1.37
USB_D_P: D1.6, U1.38
VBAT: C28.1, R11.1, TP4.1, U2.1, U5.6, U5.8
VBAT_CHG: C20.1, R11.2, TP3.1, U4.13, U4.14, U5.7
VBUS: C27.1, C30.1, D1.5, U4.1, USB1.A4, USB1.A9, USB1.B4, USB1.B9
VFBSMPS: C9.1, L2.2, U1.31
VLXSMPS: L1.1, U1.33

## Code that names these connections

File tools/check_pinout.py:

#!/usr/bin/env python3
"""Sprawdza mape wyprowadzen procesora wobec danych ST.

Trzy pytania, na kazde osobna odpowiedz:

  1. Czy to, co wyszlo na plytke, zgadza sie z tym, co zamierzylismy?
     (tablica `ZAMIAR` nizej wobec pliku `.kicad_pcb`)
  2. Czy funkcja, ktorej od nozki wymagamy, naprawde na niej istnieje?
     (tablica `ZAMIAR` wobec `STM32WB55CGUx.xml` od ST)
  3. Czy zadna nozka nie zostala pominieta ani uzyta dwa razy?

Po co to w ogole jest
---------------------
Rewizja 1 trackera opierala mape wyprowadzen na tekscie wyciagnietym
z PDF-a i wyszly z tego dwa falszywe wnioski o pinach - wiersze zginely
przy konwersji. Blad tego rodzaju nie daje sie zauwazyc ani na schemacie,
ani na renderze: widac go dopiero przy uruchamianiu, na gotowej plytce,
jako peryferial, ktory milczy. Ten skrypt kosztuje sekunde i zamyka ten
rodzaj pomylki raz na zawsze.

`ZAMIAR` jest tutaj CELOWO przepisany recznie, a nie czytany z `mcu.ato`.
Gdyby byl czytany, sprawdzalby plik sam ze soba. Tak jak jest, trzeba go
dopisac przy kazdej zmianie przypisania - i to jest ta chwila, w ktorej
czlowiek patrzy w karte katalogowa po raz drugi.

Zrodlo danych ST: `STM32_open_pin_data/mcu/STM32WB55CGUx.xml`
(github.com/STMicroelectronics/STM32_open_pin_data), wgrane do `tools/`,
zeby sprawdzenie dzialalo bez sieci. Ten sam plik, z ktorego generowany
jest CubeMX.

    python3 tools/check_pinout.py        # kod wyjscia 1, jesli cos nie gra
"""

from __future__ import annotations

import re
import sys
import xml.etree.ElementTree as ET
from pathlib import Path

PROJECT = Path(__file__).resolve().parent.parent
PCB = PROJECT / "layouts" / "dev" / "dev.kicad_pcb"
XML = Path(__file__).resolve().parent / "STM32WB55CGUx.xml"
FOOTPRINT = "STM32WB55CGU6"

# nozka -> (nazwa sieci na plytce, wymagana funkcja ST albo None)
#
# Uwaga przy USB: po LEWEJ stoi nazwa SIECI (`USB_D_N`), po PRAWEJ nazwa
# SYGNALU u ST (`USB_DM`). Rozjechaly sie celowo - siec musi konczyc sie
# na `_P` / `_N`, zeby KiCad widzial pare roznicowa, a nazwa sygnalu jest
# ta, ktora podaje karta katalogowa i ktorej nie wolno zmieniac.
#
# `None` tam, gdzie nozka pracuje jako zwykly GPIO - wtedy nie ma czego
# sprawdzac w danych ST poza tym, ze nozka w ogole istnieje i jest I/O.
ZAMIAR = {
    1:  ("+3V3",      None),             # VBAT
    2:  ("LSE_IN",    "RCC_OSC32_IN"),
    3:  ("LSE_OUT",   "RCC_OSC32_OUT"),
    4:  ("BOOT0",     None),
    5:  ("PMIC_SCL",  "I2C1_SCL"),
    6:  ("PMIC_SDA",  "I2C1_SDA"),
    7:  ("NRST",      None),
    8:  ("+3V3",      None),             # VDDA
    9:  ("CC1",       "ADC1_IN5"),
    10: ("CC2",       "ADC1_IN6"),
    11: ("PA2",       None),             # wolna
    12: ("PA3",       None),             # wolna
    13: ("SD_CS",     None),             # GPIO, nie SPI1_NSS - patrz interfaces.ato
    14: ("SD_CLK",    "SPI1_SCK"),
    15: ("SD_MISO",   "SPI1_MISO"),
    16: ("SD_MOSI",   "SPI1_MOSI"),
    17: ("PA8",       None),             # wolna
    18: ("PA9",       None),             # wolna
    19: ("CHG_STAT",  None),
    20: ("+3V3",      None),             # VDD
    21: ("RF1",       "RF_RF1"),
    22: ("GND",       None),             # VSSRF
    23: ("+3V3",      None),             # VDDRF
    24: ("OSC_OUT",   "RCC_OSC_OUT"),
    25: ("OSC_IN",    "RCC_OSC_IN"),
    26: ("AT0_NC",    None),             # test produkcyjny ST - nigdzie nie prowadzi
    27: ("AT1_NC",    None),             # test produkcyjny ST - nigdzie nie prowadzi
    28: ("CHG_INT",   None),
    29: ("CHG_CE",    None),
    30: ("CHG_PG",    None),
    31: ("VFBSMPS",   None),
    32: ("GND",       None),             # VSSSMPS
    33: ("VLXSMPS",   None),
    34: ("+3V3",      None),             # VDDSMPS
    35: ("+3V3",      None),             # VDD
    36: ("PA10",      None),             # wolna
    37: ("USB_D_N",   "USB_DM"),
    38: ("USB_D_P",   "USB_DP"),
    39: ("SWDIO",     "SYS_JTMS-SWDIO"),
    40: ("+3V3",      None),             # VDDUSB
    41: ("SWCLK",     "SYS_JTCK-SWCLK"),
    42: ("EXT_CS",    None),             # CS ukladu zewnetrznego na SPI1
    43: ("SWO",       "SYS_JTDO-SWO"),
    44: ("GAUGE_INT", None),
    45: ("EXP_INT",   None),             # przerwanie z ekspandera TCA6408A
    46: ("PB6",       None),             # wolna
    47: ("PB7",       None),             # wolna
    48: ("+3V3",      None),             # VDD
    49: ("GND",       None),             # pad pod obudowa - JEDYNA masa ukladu
}


def poddrzewa(text: str, head: str):
    """Kolejne zrownowazone s-wyrazenia zaczynajace sie od `head`."""
    start = 0
    while True:
        i = text.find(head, start)
        if i < 0:
            return
        d = j = 0
        j = i
        instr = esc = False
        while True:
            ch = text[j]
            if instr:
                if esc:
                    esc = False
                elif ch == "\\":
                    esc = True
                elif ch == '"':
                    instr = False
            elif ch == '"':
                instr = True
            elif ch == "(":
                d += 1
            elif ch == ")":
                d -= 1
                if d == 0:
                    j += 1
                    break
            j += 1
        yield text[i:j]
        start = j


def z_plytki() -> dict[int, str | None]:
    text = PCB.read_text(encoding="utf8")
    fps = [b for b in poddrzewa(text, "(footprint ") if FOOTPRINT in b.split("\n")[0]]
    if len(fps) != 1:
        sys.exit(f"na plytce jest {len(fps)} ukladow {FOOTPRINT}, oczekiwano 1")
    out = {}
    for pb in poddrzewa(fps[0], "(pad "):
        num = re.match(r'\(pad "([^"]+)"', pb).group(1)
        net = re.search(r'\(net \d+ "([^"]*)"\)', pb)
        out[int(num)] = net.group(1) if net else None
    return out


def ze_st() -> dict[int, tuple[str, set[str]]]:
    ns = {"m": "http://dummy.com"}
    root = ET.parse(XML).getroot()
    return {int(p.get("Position")): (p.get("Name"),
                                     {s.get("Name") for s in p.findall("m:Signal", ns)})
            for p in root.findall("m:Pin", ns)}


def main() -> int:
    plytka = z_plytki()
    st = ze_st()
    bledy: list[str] = []

    if len(st) != 48:
        bledy.append(f"plik ST opisuje {len(st)} nozek, a UFQFPN-48 ma 48")

    for nozka, (siec, funkcja) in sorted(ZAMIAR.items()):
        nazwa = st[nozka][0] if nozka in st else "EP"
        realna = plytka.get(nozka)

        if siec is None:
            # Nozka ma zostac bez sieci. atopile nadaje takiej wlasna siec
            # jednopadowa nazwana jak numer nozki - to tez znaczy "wolna".
            if realna not in (None, str(nozka)):
                bledy.append(f"nozka {nozka} ({nazwa}) miala zostac wolna, "
                             f"a jest na sieci {realna!r}")
            continue

        if realna != siec:
            bledy.append(f"nozka {nozka} ({nazwa}): zamiar {siec!r}, "
                         f"na plytce {realna!r}")

        if funkcja and funkcja not in st[nozka][1]:
            bledy.append(f"nozka {nozka} ({nazwa}): wymagamy funkcji "
                         f"{funkcja!r}, a ST jej na tej nozce NIE MA "
                         f"(ma: {', '.join(sorted(st[nozka][1])) or 'nic'})")

    brakuje = sorted(set(range(1, 50)) - set(ZAMIAR))
    if brakuje:
        bledy.append(f"ZAMIAR nie opisuje nozek: {brakuje}")

    nadmiarowe = sorted(set(plytka) - set(ZAMIAR))
    if nadmiarowe:
        bledy.append(f"na plytce sa nozki spoza ZAMIARU: {nadmiarowe}")

    # Dwie rozne nozki na tej samej sieci sa dozwolone tylko dla zasilania
    # i masy. Wszedzie indziej to zwarcie, ktorego nikt nie chcial.
    wspolne = {}
    for nozka, (siec, _) in ZAMIAR.items():
        if siec and siec not in ("+3V3", "GND"):
            wspolne.setdefault(siec, []).append(nozka)
    for siec, nozki in wspolne.items():
        if len(nozki) > 1:
            bledy.append(f"siec {siec!r} siedzi na nozkach {nozki} - "
                         f"zwarcie albo literowka w ZAMIARZE")

    # `_NC` to nozki, ktore maja NAZWE sieci, ale ta siec nigdzie nie
    # prowadzi - jeden pad i tyle. Nazwa istnieje po to, zeby atopile nie
    # ochrzcilo ich numerem nozki; numer potrafi wejsc w kolizje
    # z numeracja, na ktora wskazuja wylewki. Liczac "obsadzone" trzeba je
    # odjac, inaczej podsumowanie twierdzi, ze obsadzonych jest wiecej niz
    # nozek.
    nc = [s for s, _ in ZAMIAR.values() if s and s.endswith("_NC")]
    uzyte = len([1 for s, _ in ZAMIAR.values() if s]) - len(nc)
    sprawdzone = len([1 for _, f in ZAMIAR.values() if f])
    if bledy:
        print(f"BLEDY ({len(bledy)}):")
        for b in bledy:
            print("  -", b)
        return 1
    print(f"mapa wyprowadzen OK: 48 nozek + pad, {uzyte} obsadzonych, "
          f"{len(nc)} nigdzie nie prowadzi ({', '.join(sorted(nc))}), "
          f"{sprawdzone} funkcji sprawdzonych wobec STM32WB55CGUx.xml")
    return 0


if __name__ == "__main__":
    sys.exit(main())

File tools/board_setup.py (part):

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        # In2, In3 i B.Cu - a tam moga lezec cudze sciezki. Pierwsze
        # uruchomienie tego kodu postawilo pod U3 i U5 komplet przelotek
        # w miedzi padu i zrobilo 18 zwarc z SD_CLK, SD_MISO, SD_MOSI,
        # PB6, CHG_CE, CHG_PG i GAUGE_INT na warstwach wewnetrznych.
        # Stawiamy wiec tylko tam, gdzie nic obcego nie przeszkadza.
        promien = mm(PAD_VIA_DIA_MM / 2) + mm(CLEARANCE_MM)
        obce = []
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            zmienione += 1

    # Napisy wlasne, dopisane w KiCadzie - na tej plytce mapa pinow listew
    # (`+3V3`, `GND`, `SCL`, `PA2`, `RST`, `BOOT0`, `LD1`...). Tych NIE
    # zmniejszamy: ktos dobral im wysokosc 1,0 mm swiadomie, a to one sa
    # czytane przy wpinaniu przewodu, nie oznaczenia elementow.
    #
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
